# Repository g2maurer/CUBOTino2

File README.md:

# CUBOTino2
 CUBOTino Modifications:
 1. No changes were made to software.
 2. Designed PCB (shield) to connect with RPi board.
 3. Modified cover STL file to be able to mount Display.
 4. Display is now cabled to PCB, not directly attached.
 5. Added photos in Images to help explain board connections and Display mounting.
 6. Photo DisplayMountScrews provides the part number for the screws used to mount the display. Screws were purchased from McMaster-Carr.
 7. The Bill of Materials (BOM) in found in the file PCB/CUBOTino2.csv
 8. The schematic is in the file PCB/CUBOTino2.pdf
 9. See file PCB/SMD Parts.txt for part sourcing info.

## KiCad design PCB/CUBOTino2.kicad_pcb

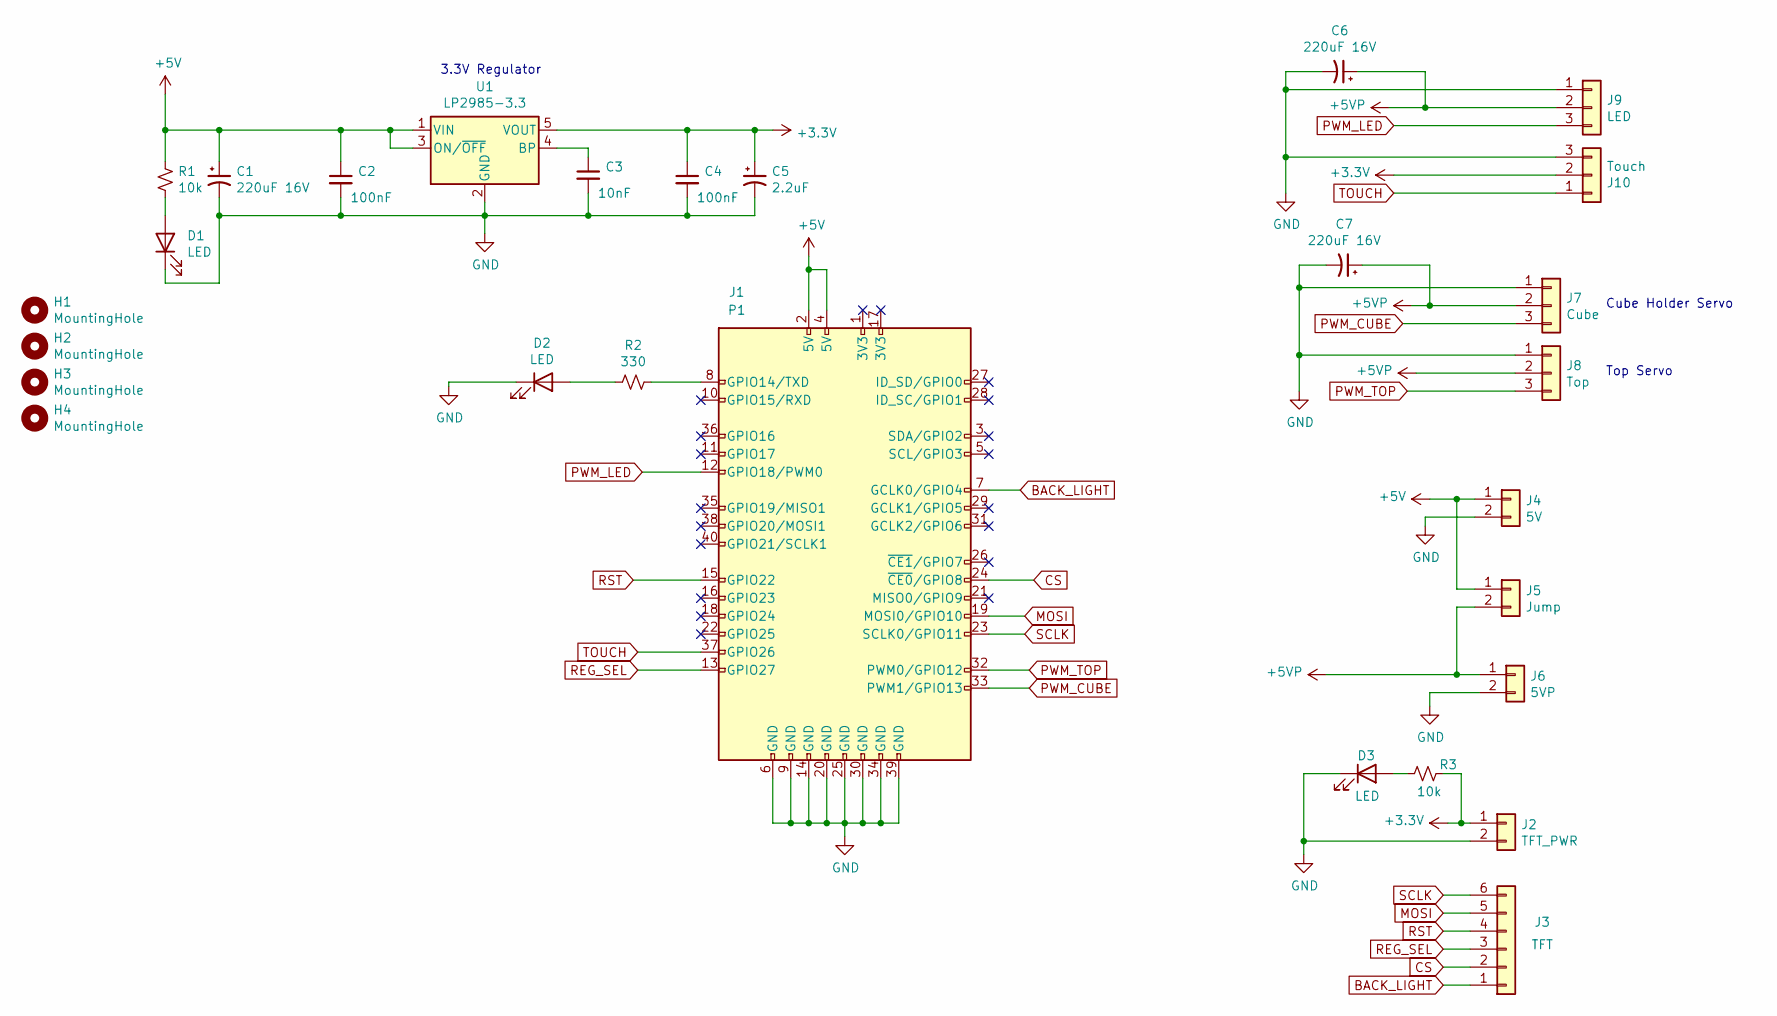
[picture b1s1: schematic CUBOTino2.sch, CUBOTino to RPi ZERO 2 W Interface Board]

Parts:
C1, C6, C7: 220uF 16V; C_Radial_D5.0mm_H7.0mm_P2.00mm
C2, C4: 100nF; C_0805_2012Metric_Pad1.18x1.45mm_HandSolder
C3: 10nF; C_0805_2012Metric_Pad1.18x1.45mm_HandSolder
C5: 2.2uF; C_1206_3216Metric_Pad1.33x1.80mm_HandSolder
D1, D3: LED; LED_0805_2012Metric_Pad1.15x1.40mm_HandSolder
D2: LED; LED_1206_3216Metric_Pad1.42x1.75mm_HandSolder
H1, H2, H3, H4: MountingHole; MountingHole_2.7mm
J1: P1; PinSocket_2x20_P2.54mm_Vertical
J2: TFT_PWR; JST_XH_B2B-XH-A_1x02_P2.50mm_Vertical
J3: TFT; JST_XH_B6B-XH-A_1x06_P2.50mm_Vertical
J4: 5V; JST_XH_B2B-XH-A_1x02_P2.50mm_Vertical
J5: Jump; PinHeader_1x02_P2.54mm_Vertical
J6: 5VP; JST_XH_B2B-XH-A_1x02_P2.50mm_Vertical
J7: Cube; PinHeader_1x03_P2.54mm_Horizontal
J8: Top; PinHeader_1x03_P2.54mm_Horizontal
J9: LED; JST_XH_B3B-XH-A_1x03_P2.50mm_Vertical
J10: Touch; JST_XH_B3B-XH-A_1x03_P2.50mm_Vertical
R1, R3: 10k; R_0805_2012Metric_Pad1.20x1.40mm_HandSolder
R2: 330; R_0805_2012Metric_Pad1.20x1.40mm_HandSolder
U1: LP2985-3.3; SOT-23-5

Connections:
+3V3: C4.1, C5.1, J2.1, J10.2, R3.2, U1.5 (VOUT)
+5V: C1.1, C2.1, J1.2 (5V), J1.4 (5V), J4.1, J5.1, R1.2, U1.1 (VIN), U1.3 (ON/~OFF~)
+5VP: C6.1, C7.1, J5.2, J6.1, J7.2, J8.2, J9.2
BACK_LIGHT: J1.7 (GCLK0/GPIO4), J3.1
CS: J1.24 (~CE0~/GPIO8), J3.2
GND: C1.2, C2.2, C3.2, C4.2, C5.2, C6.2, C7.2, D1.1 (K), D2.1 (K), D3.1 (K), J1.6 (GND), J1.9 (GND), J1.14 (GND), J1.20 (GND), J1.25 (GND), J1.30 (GND), J1.34 (GND), J1.39 (GND), J2.2, J4.2, J6.2, J7.1, J8.1, J9.1, J10.3, U1.2 (GND)
MOSI: J1.19 (MOSI0/GPIO10), J3.5
unnamed: C3.1, U1.4 (BP)
unnamed: D1.2 (A), R1.1
unnamed: D2.2 (A), R2.1
unnamed: D3.2 (A), R3.1
unnamed: J1.8 (GPIO14/TXD), R2.2
PWM_CUBE: J1.33 (PWM1/GPIO13), J7.3
PWM_LED: J1.12 (GPIO18/PWM0), J9.3
PWM_TOP: J1.32 (PWM0/GPIO12), J8.3
REG_SEL: J1.13 (GPIO27), J3.3
RST: J1.15 (GPIO22), J3.4
SCLK: J1.23 (SCLK0/GPIO11), J3.6
TOUCH: J1.37 (GPIO26), J10.1

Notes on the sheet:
Cube Holder Servo
Top Servo
3.3V Regulator

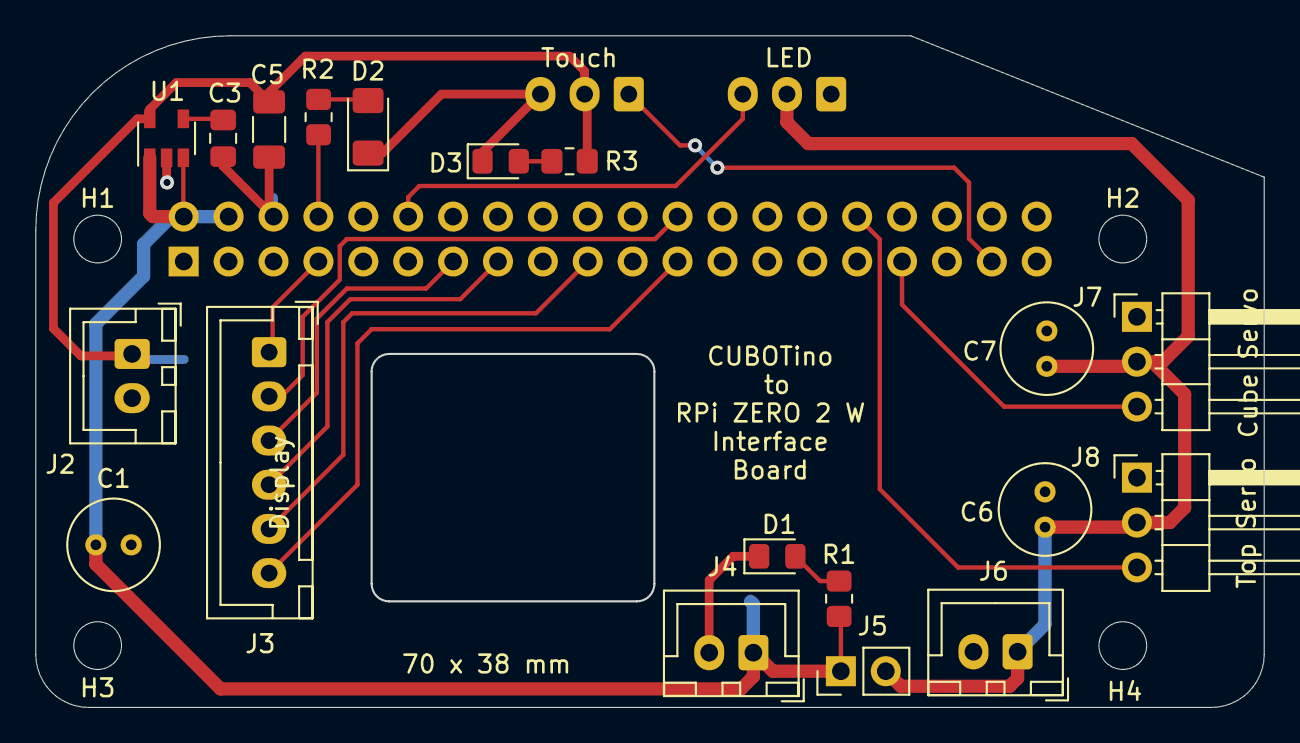
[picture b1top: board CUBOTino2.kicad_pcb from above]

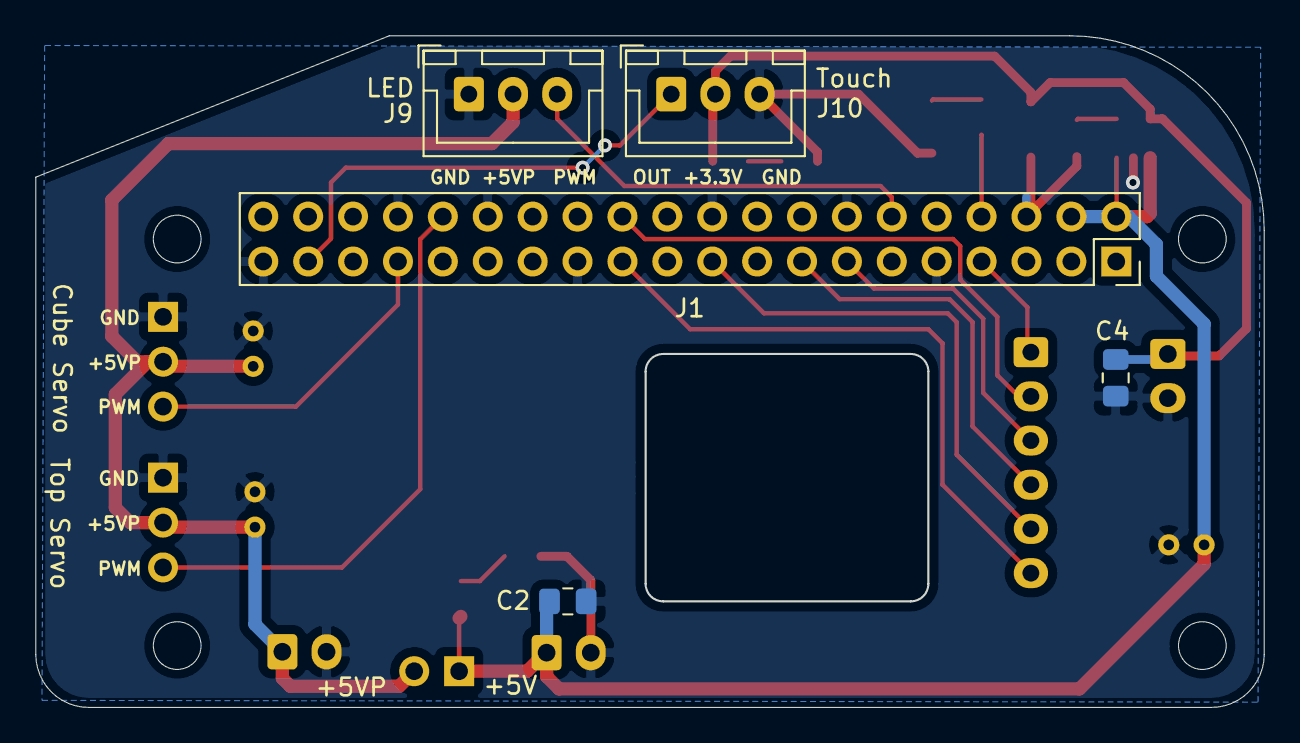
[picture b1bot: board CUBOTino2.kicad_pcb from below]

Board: 2 copper layers, 69.4 x 37.9 mm, 28 parts (5 on the bottom side), 19 nets.

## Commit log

2023-11-09 CUBOTino modifications
    Modifications:
2023-11-09 Adding STL files
    Added files that were modified to use PCB design.
2023-11-09 Added Photos
    Added photos to help explain the board connections and display mounting.
2023-11-09 Added additional Photos
    Added PCB Photos
2024-01-01 Update README.md
    Added more information.
2024-01-01 Create SMD parts.txt
    Added file to help with acquiring surface mount parts.
2024-01-01 Update README.md
    SMD part info.
2024-01-01 Update README.md
    Correction
